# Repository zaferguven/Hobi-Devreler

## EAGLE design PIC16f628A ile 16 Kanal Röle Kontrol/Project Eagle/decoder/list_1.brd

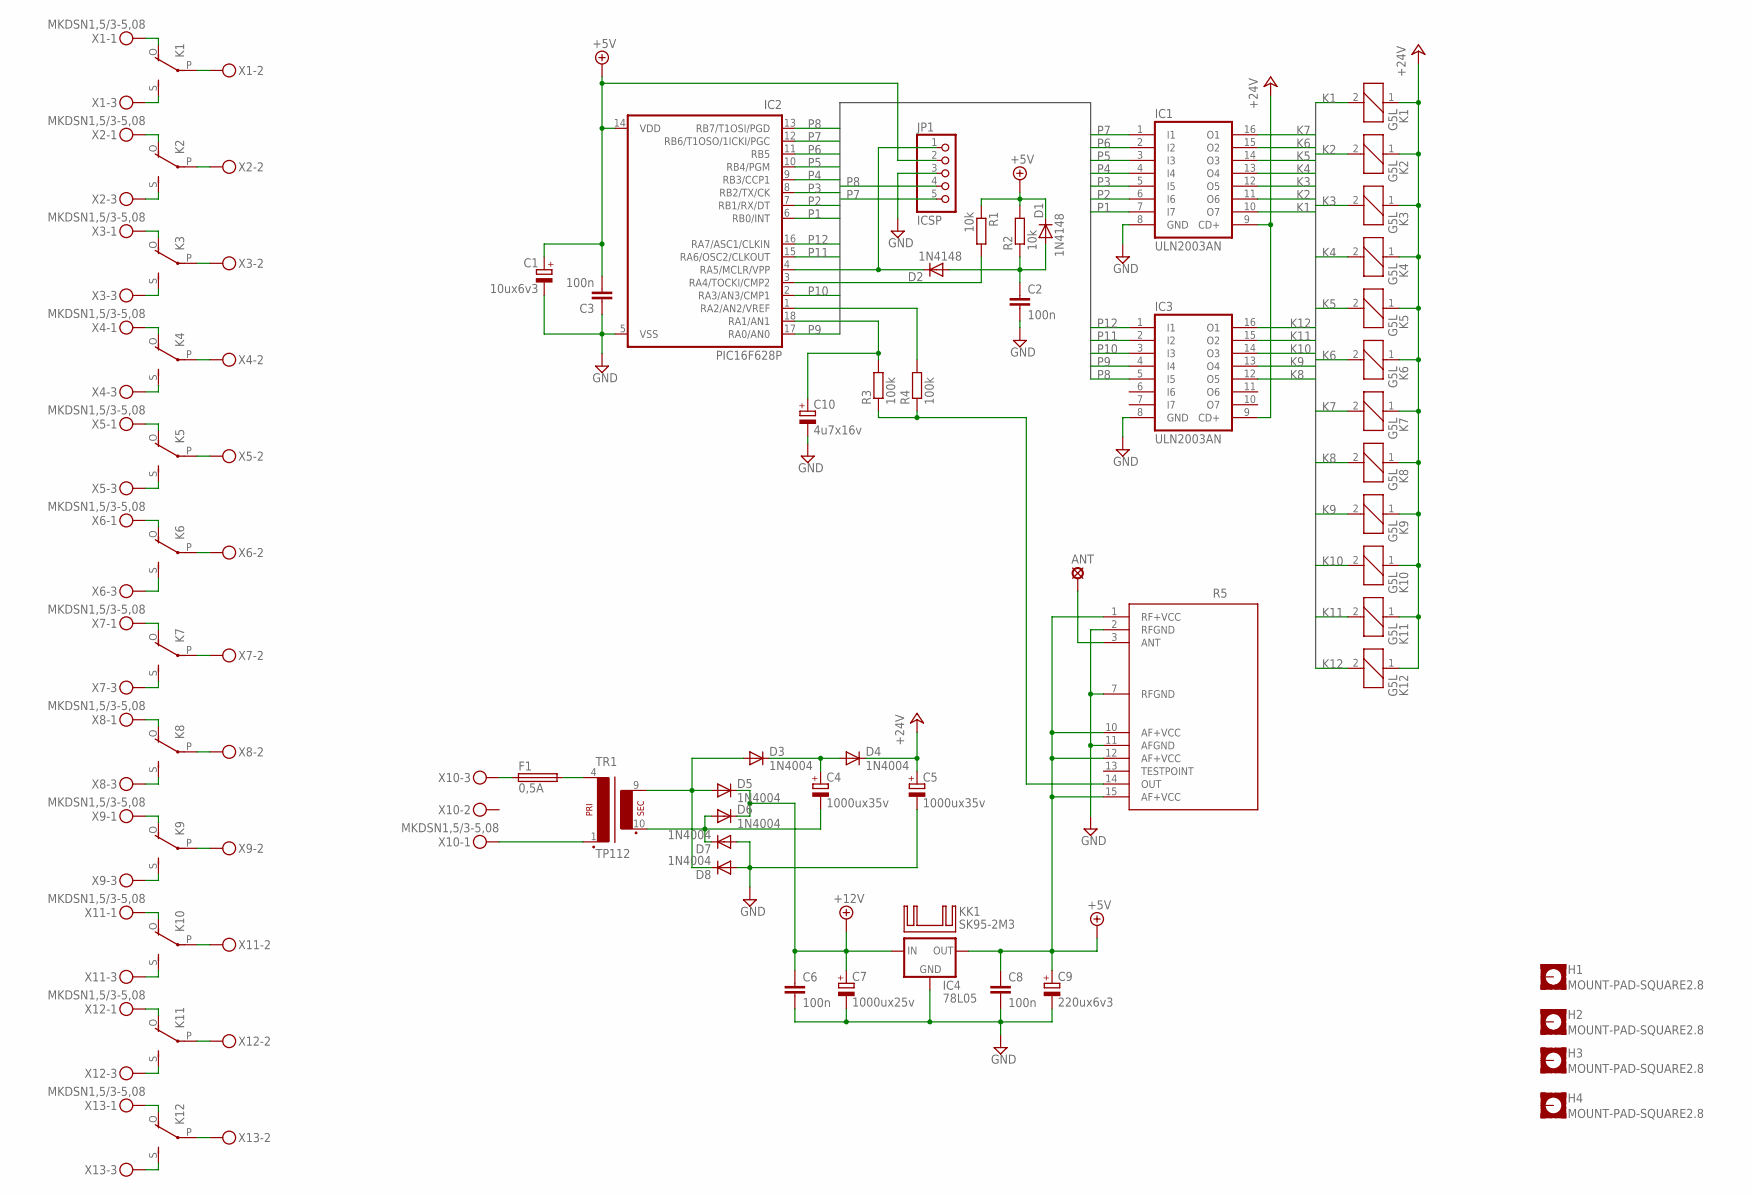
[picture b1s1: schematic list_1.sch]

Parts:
ANT: SE14
C1: 10ux6v3; E2,5-5
C2, C3, C6, C8: 100n; C050-025X075
C4: 1000ux35v; E3,5-8
C5: 1000ux35v; E3,5-10
C7: 1000ux25v; E3,5-8
C9: 220ux6v3; E2,5-5
C10: 4u7x16v; E2,5-5
D1, D2: 1N4148; DO35-10
D3, D4, D5, D6, D7, D8: 1N4004; DO41-10
F1: 0,5A; SHK20L
H1, H2, H3, H4: MOUNT-PAD-SQUARE2.8; 2,8-PAD-SQUARE
IC1, IC3: ULN2003AN; DIL16
IC2: PIC16F628P; DIL18
IC4: 78L05; 78XXS
JP1: ICSP; 1X05
K1, K2, K3, K4, K5, K6, K7, K8, K9, K10, K11, K12: G5L; G5LE
KK1: SK95-2M3
R1, R2: 10k; 0207/10
R3, R4: 100k; 0207/10
R5: RR10; RR10V
TR1: TP112; TR112
X1, X2, X3, X4, X5, X6, X7, X8, X9, X10, X11, X12, X13: MKDSN1,5/3-5,08

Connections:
+5V: C1.+, C3.2, C8.1, C9.+, D1.C, IC2.14 (VDD), IC4.OUT, JP1.2, R1.1, R2.2, R5.1 (RF+VCC), R5.10 (AF+VCC), R5.12 (AF+VCC), R5.15 (AF+VCC)
+12V: C6.1, C7.+, D5.C, D6.C, IC4.IN
+24V: C5.+, D4.C, IC1.9 (CD+), IC3.9 (CD+), K1.1, K2.1, K3.1, K4.1, K5.1, K6.1, K7.1, K8.1, K9.1, K10.1, K11.1, K12.1
GND: C1.-, C2.2, C3.1, C5.-, C6.2, C7.-, C8.2, C9.-, C10.-, D7.A, D8.A, IC1.8 (GND), IC2.5 (VSS), IC3.8 (GND), IC4.GND, JP1.3, R5.2 (RFGND), R5.7 (RFGND), R5.11 (AFGND)
K1: IC1.10 (O7), K1.2
K2: IC1.11 (O6), K2.2
K3: IC1.12 (O5), K3.2
K4: IC1.13 (O4), K4.2
K5: IC1.14 (O3), K5.2
K6: IC1.15 (O2), K6.2
K7: IC1.16 (O1), K7.2
K8: IC3.12 (O5), K8.2
K9: IC3.13 (O4), K9.2
K10: IC3.14 (O3), K10.2
K11: IC3.15 (O2), K11.2
K12: IC3.16 (O1), K12.2
unnamed: K2.S, X2.3
unnamed: K1.P, X1.2
unnamed: K1.S, X1.3
unnamed: K1.O, X1.1
unnamed: K2.O, X2.1
unnamed: K2.P, X2.2
unnamed: K3.P, X3.2
unnamed: K3.S, X3.3
unnamed: K3.O, X3.1
unnamed: K4.O, X4.1
unnamed: K4.P, X4.2
unnamed: K4.S, X4.3
unnamed: K5.P, X5.2
unnamed: K5.O, X5.1
unnamed: K5.S, X5.3
unnamed: K6.P, X6.2
unnamed: K6.O, X6.1
unnamed: K6.S, X6.3
unnamed: K7.P, X7.2
unnamed: K7.O, X7.1
unnamed: K7.S, X7.3
unnamed: K8.P, X8.2
unnamed: K9.P, X9.2
unnamed: K10.P, X11.2
unnamed: K11.P, X12.2
unnamed: K12.P, X13.2
unnamed: K8.O, X8.1
unnamed: K8.S, X8.3
unnamed: K9.O, X9.1
unnamed: K9.S, X9.3
unnamed: K10.O, X11.1
unnamed: K10.S, X11.3
unnamed: K11.O, X12.1
unnamed: K11.S, X12.3
unnamed: K12.O, X13.1
unnamed: K12.S, X13.3
unnamed: C10.+, IC2.18 (RA1/AN1), R3.2
unnamed: IC2.1 (RA2/AN2/VREF), R4.2
unnamed: R3.1, R4.1, R5.14 (OUT)
unnamed: D2.C, IC2.4 (RA5/MCLR/VPP), JP1.1
unnamed: IC2.3 (RA4/TOCKI/CMP2), R1.2
unnamed: C2.1, D1.A, D2.A, R2.1
unnamed: ANT.MP, R5.3 (ANT)
unnamed: F1.2A, TR1.4 (P1)
unnamed: TR1.1 (P2), X10.1
unnamed: F1.1A, X10.3
unnamed: C4.-, D6.A, D7.C, TR1.10 (S3)
unnamed: D3.A, D5.A, D8.C, TR1.9 (S4)
unnamed: C4.+, D3.C, D4.A
P1: IC1.7 (I7), IC2.6 (RB0/INT)
P2: IC1.6 (I6), IC2.7 (RB1/RX/DT)
P3: IC1.5 (I5), IC2.8 (RB2/TX/CK)
P4: IC1.4 (I4), IC2.9 (RB3/CCP1)
P5: IC1.3 (I3), IC2.10 (RB4/PGM)
P6: IC1.2 (I2), IC2.11 (RB5)
P7: IC1.1 (I1), IC2.12 (RB6/T1OSO/1ICKI/PGC), JP1.5
P8: IC2.13 (RB7/T1OSI/PGD), IC3.5 (I5), JP1.4
P9: IC2.17 (RA0/AN0), IC3.4 (I4)
P10: IC2.2 (RA3/AN3/CMP1), IC3.3 (I3)
P11: IC2.15 (RA6/OSC2/CLKOUT), IC3.2 (I2)
P12: IC2.16 (RA7/ASC1/CLKIN), IC3.1 (I1)

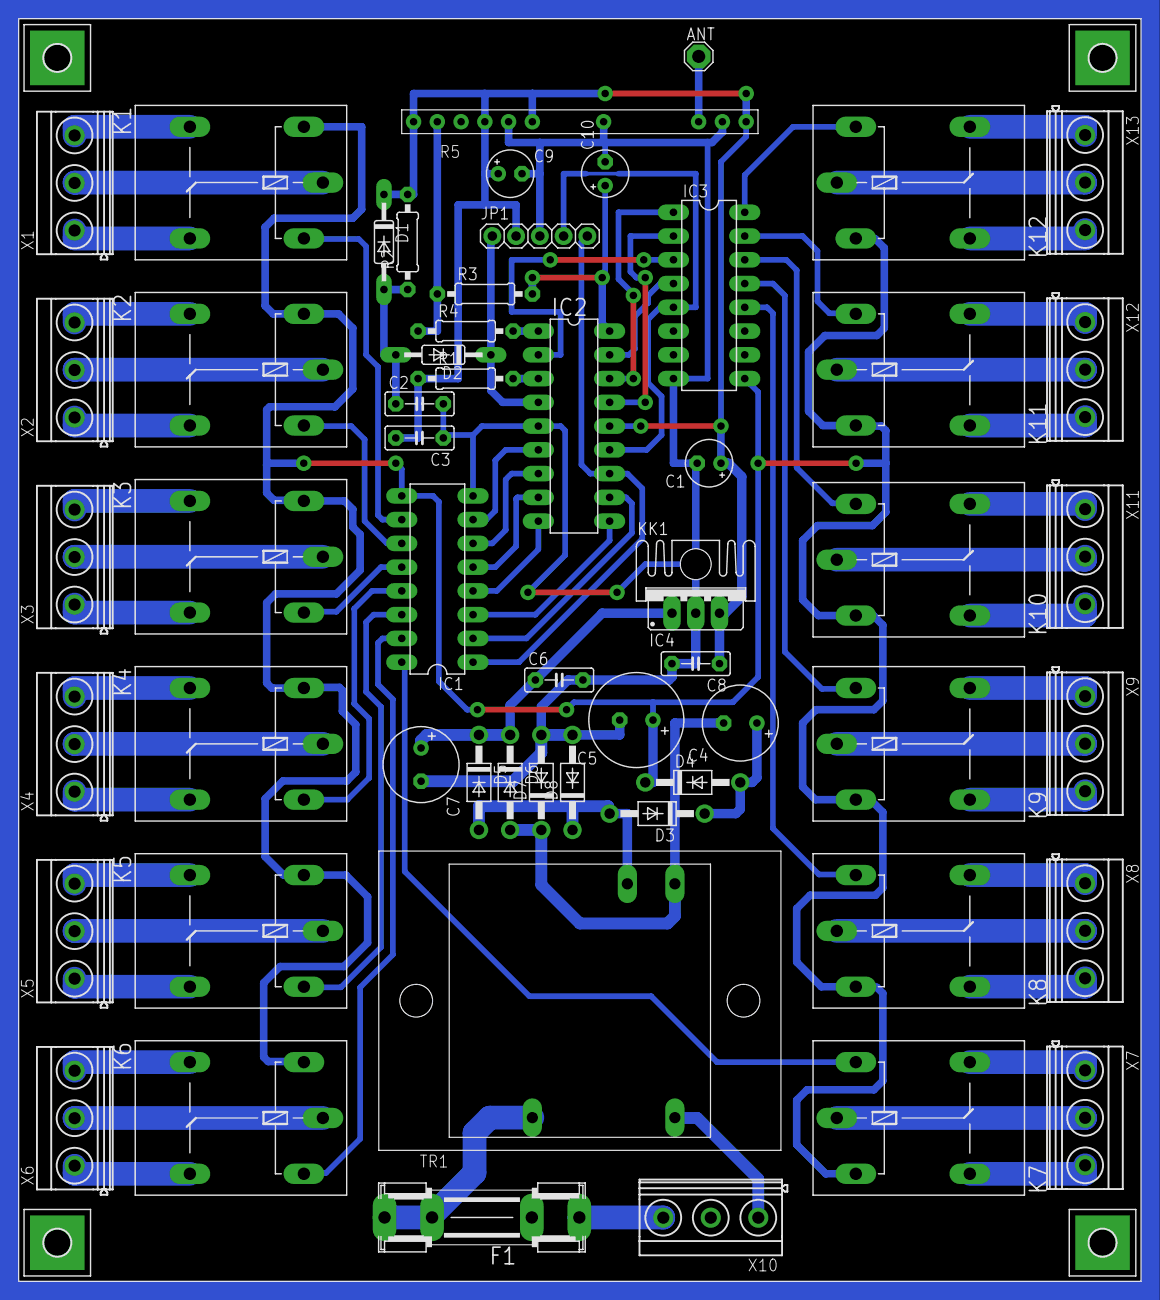
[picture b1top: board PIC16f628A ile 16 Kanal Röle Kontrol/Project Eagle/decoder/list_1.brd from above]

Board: 2 copper layers, 120.0 x 135.0 mm, 61 parts (0 on the bottom side), 77 nets.

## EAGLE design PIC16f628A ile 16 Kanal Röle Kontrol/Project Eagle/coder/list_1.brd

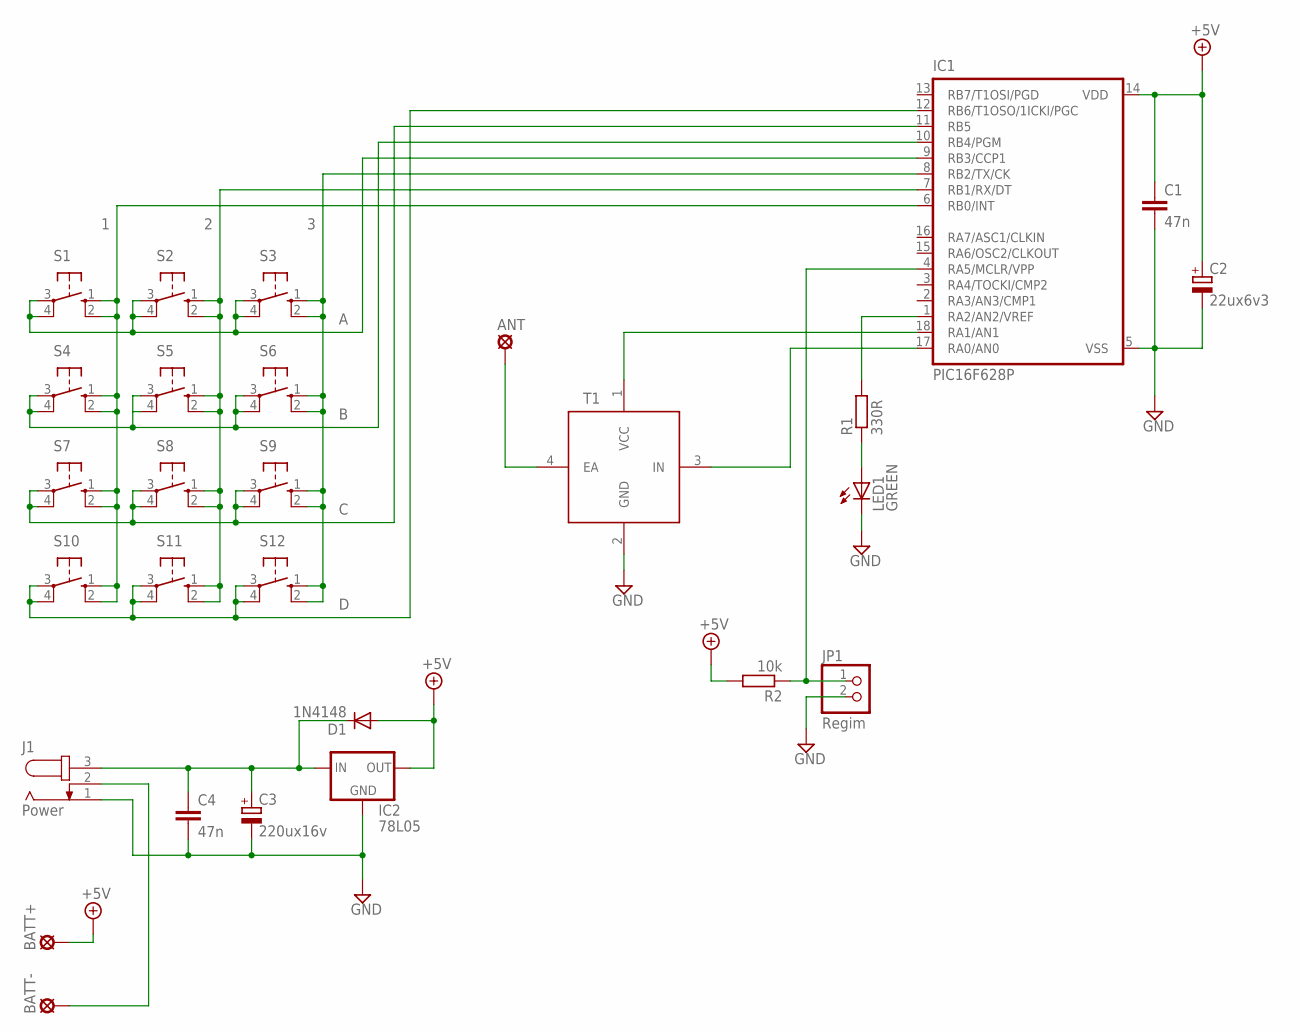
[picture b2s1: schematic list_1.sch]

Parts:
ANT: SE11
BATT+: SE11
BATT-: SE11
C1, C4: 47n; C050-025X075
C2: 22ux6v3; E2,5-5
C3: 220ux16v; E2,5-5
D1: 1N4148; DO35-7
IC1: PIC16F628P; DIL18
IC2: 78L05; 78LXX
J1: Power; SPC4077
JP1: Regim; 1X02
LED1: GREEN; LED3MM
R1: 330R; 0207/10
R2: 10k; 0207/10
S1, S2, S3, S4, S5, S6, S7, S8, S9, S10, S11, S12: 40-XX; B3F-40XX
T1: RT4

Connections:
+5V: BATT+.MP, C1.1, C2.+, D1.A, IC1.14 (VDD), IC2.OUT, R2.2
GND: C1.2, C2.-, C3.-, C4.2, IC1.5 (VSS), IC2.GND, J1.1, JP1.2, LED1.K (C), T1.2 (GND)
unnamed: LED1.A, R1.1
unnamed: IC1.9 (RB3/CCP1), S1.3, S1.4 (P1), S2.3, S2.4 (P1), S3.3, S3.4 (P1)
unnamed: IC1.10 (RB4/PGM), S4.3, S4.4 (P1), S5.3, S5.4 (P1), S6.3, S6.4 (P1)
unnamed: IC1.4 (RA5/MCLR/VPP), JP1.1, R2.1
unnamed: IC1.12 (RB6/T1OSO/1ICKI/PGC), S10.3, S10.4 (P1), S11.3, S11.4 (P1), S12.3, S12.4 (P1)
unnamed: IC1.6 (RB0/INT), S1.1 (S), S1.2 (S1), S4.1 (S), S4.2 (S1), S7.1 (S), S7.2 (S1), S10.1 (S), S10.2 (S1)
unnamed: IC1.7 (RB1/RX/DT), S2.1 (S), S2.2 (S1), S5.1 (S), S5.2 (S1), S8.1 (S), S8.2 (S1), S11.1 (S), S11.2 (S1)
unnamed: IC1.8 (RB2/TX/CK), S3.1 (S), S3.2 (S1), S6.1 (S), S6.2 (S1), S9.1 (S), S9.2 (S1), S12.1 (S), S12.2 (S1)
unnamed: IC1.11 (RB5), S7.3, S7.4 (P1), S8.3, S8.4 (P1), S9.3, S9.4 (P1)
unnamed: IC1.1 (RA2/AN2/VREF), R1.2
unnamed: C3.+, C4.1, D1.C, IC2.IN, J1.3
unnamed: IC1.17 (RA0/AN0), T1.3 (IN)
unnamed: BATT-.MP, J1.2
unnamed: IC1.18 (RA1/AN1), T1.1 (VCC)
unnamed: ANT.MP, T1.4 (EA)

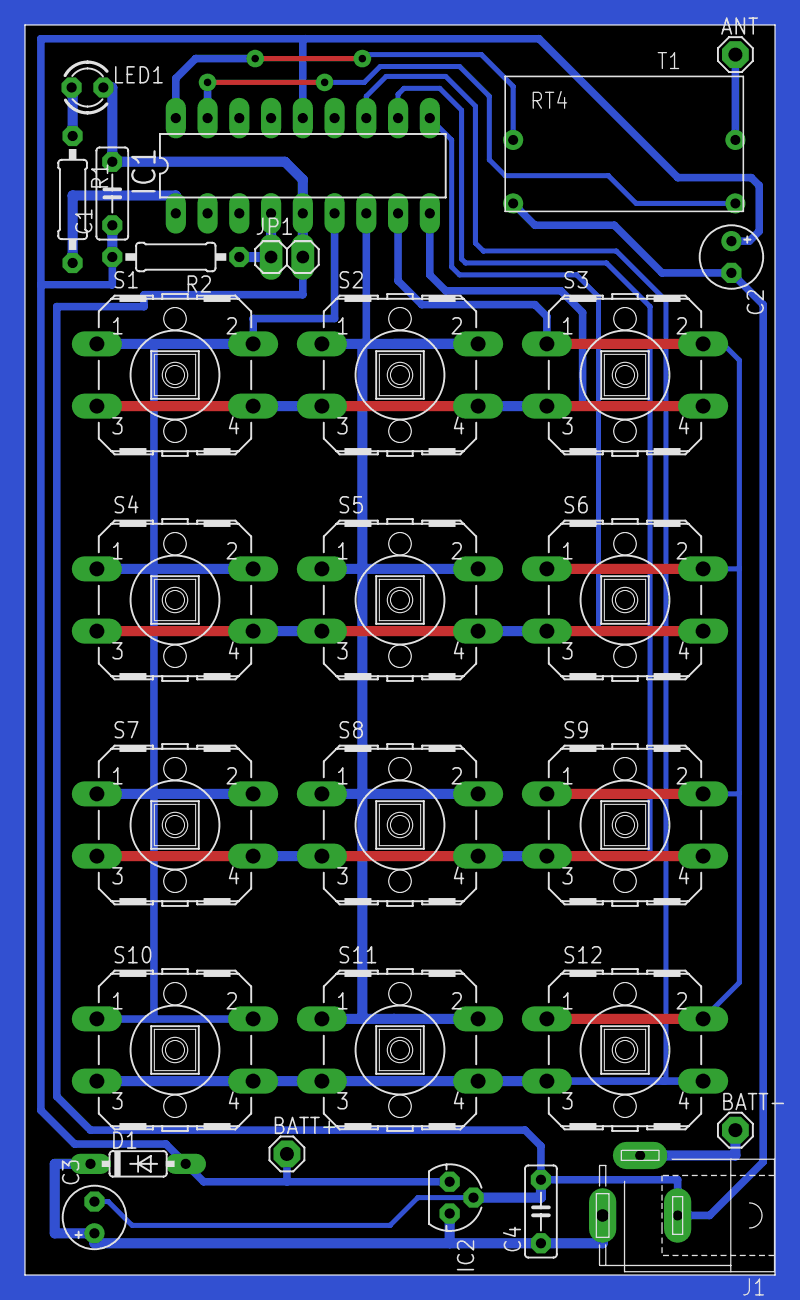
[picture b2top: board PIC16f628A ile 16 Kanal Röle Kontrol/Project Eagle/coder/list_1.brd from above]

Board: 2 copper layers, 60.0 x 100.0 mm, 28 parts (0 on the bottom side), 17 nets.
